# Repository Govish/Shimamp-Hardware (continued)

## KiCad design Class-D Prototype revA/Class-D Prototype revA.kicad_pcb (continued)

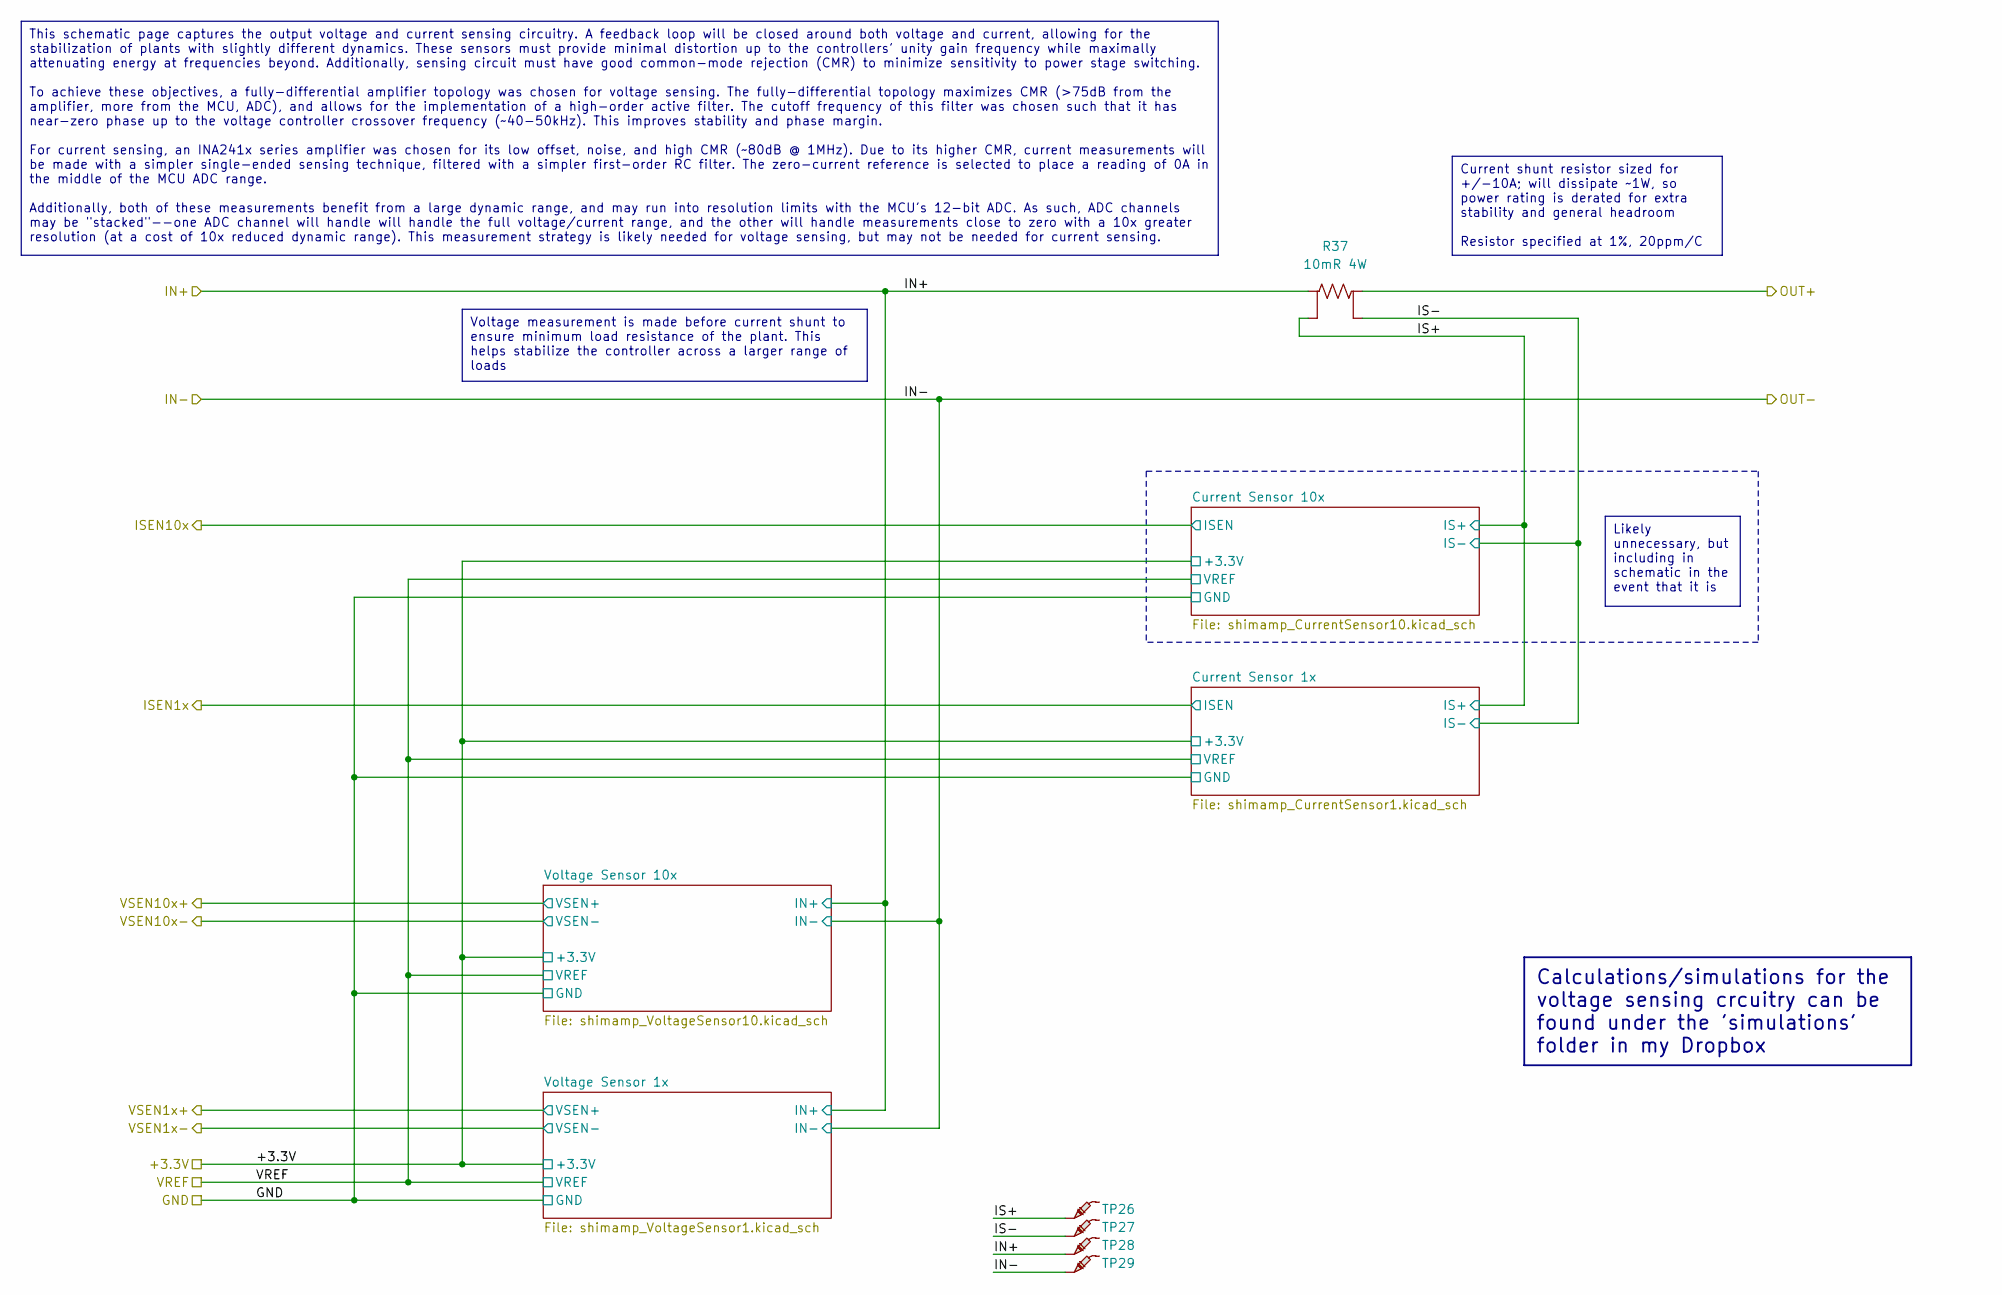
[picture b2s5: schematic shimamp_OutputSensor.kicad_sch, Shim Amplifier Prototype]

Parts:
R37: 10mR 4W; R_2512_6332_CURRENT_SHUNT; Part Number VMS-R010-1.0-U
TP26, TP27, TP28, TP29: -; TestPoint_Pad_D2.0mm

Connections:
/Output Sensor/IN+: R37.2, TP28.1; also elsewhere on the board
/Output Sensor/IN-: TP29.1; also elsewhere on the board
/Output Sensor/IS+: R37.4, TP26.1; also elsewhere on the board
/Output Sensor/IS-: R37.3, TP27.1; also elsewhere on the board
/Output Sensor/OUT+: R37.1; also elsewhere on the board

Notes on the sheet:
This schematic page captures the output voltage and current sensing circuitry. A feedback loop will be closed around both voltage and current, allowing for the stabilization of plants with slightly different dynamics. These sensors must provide minimal distortion up to the controllers' unity gain f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
Calculations/simulations for the voltage sensing crcuitry can be found under the 'simulations' folder in my Dropbox
Likely unnecessary, but including in schematic in the event that it is
Voltage measurement is made before current shunt to ensure minimum load resistance of the plant. This helps stabilize the controller across a larger range of loads
Current shunt resistor sized for +/-10A; will dissipate ~1W, so power rating is derated for extra stability and general headroom Resistor specified at 1%, 20ppm/C

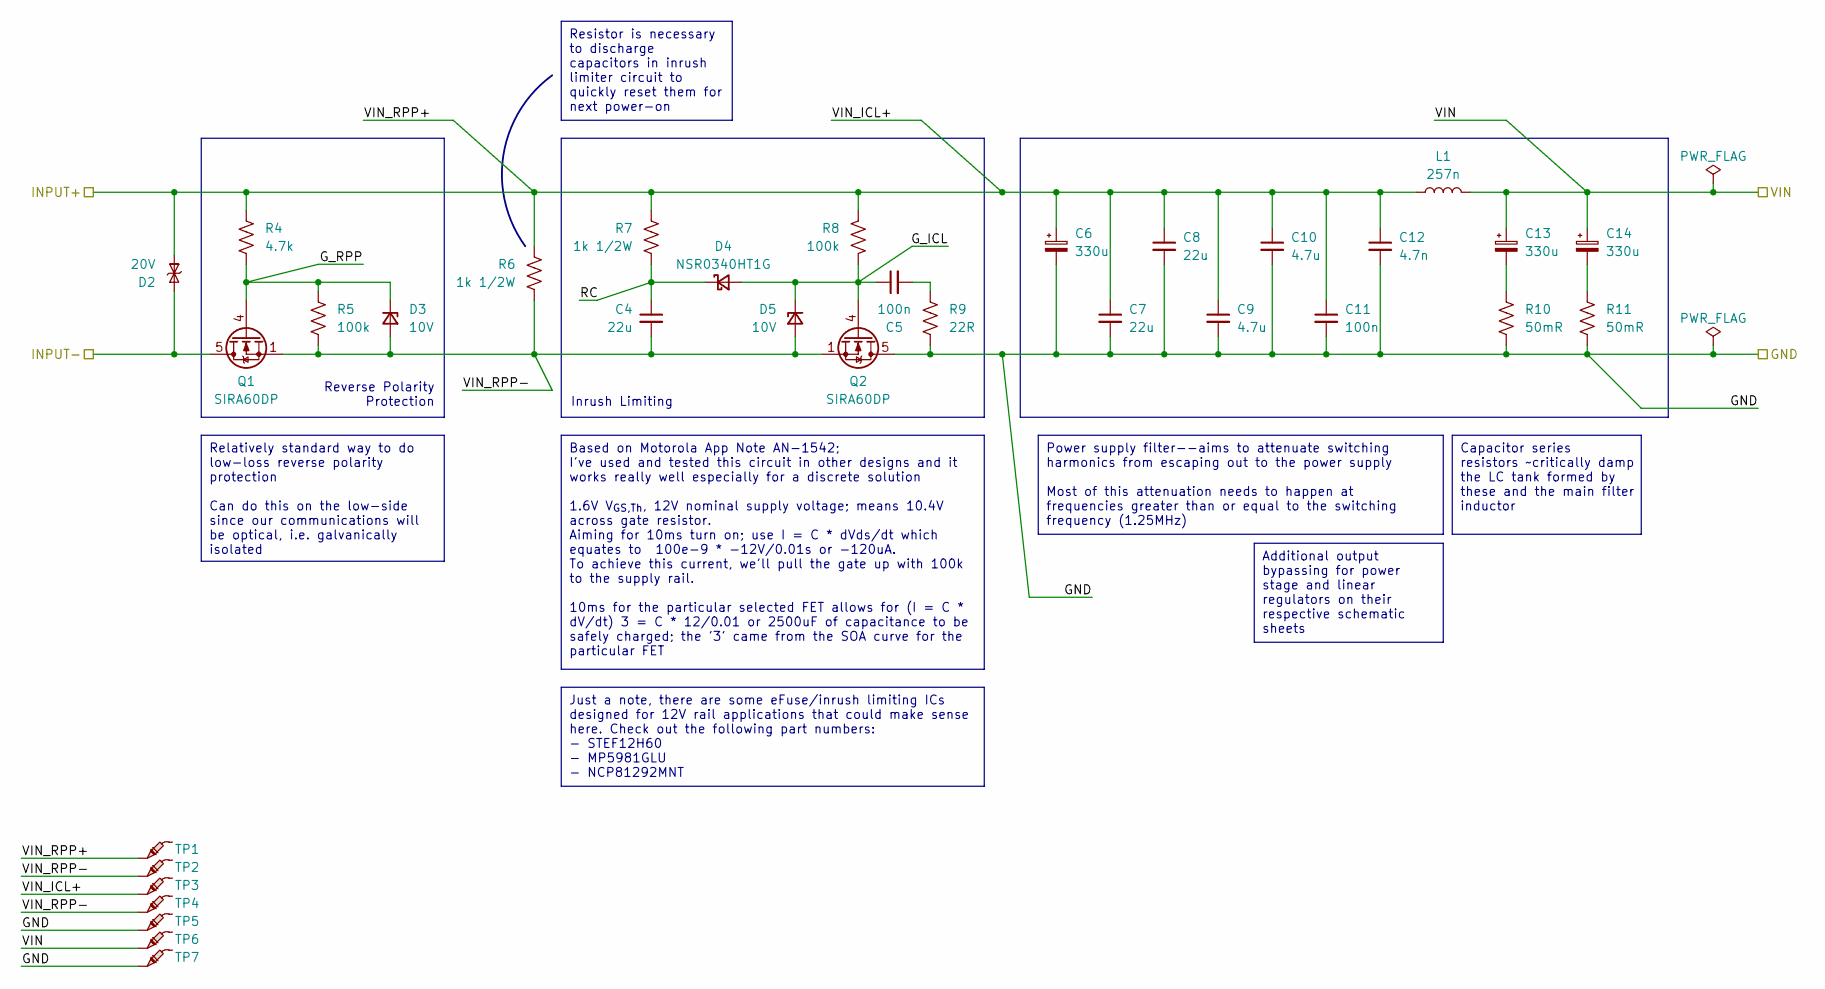
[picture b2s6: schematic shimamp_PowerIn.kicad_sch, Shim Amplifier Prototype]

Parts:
C4, C7, C8: 22u; C_1210_3225Metric_Pad1.33x2.70mm_HandSolder; Part Number CL32B226KAJNNNE
C5, C11: 100n; C_0603_1608Metric_Pad1.08x0.95mm_HandSolder; Part Number CL10B104KB8NNWC
C6, C13, C14: 330u; CP_Elec_10x12.6; Part Number 25SVPF330M
C9, C10: 4.7u; C_0805_2012Metric_Pad1.18x1.45mm_HandSolder; Part Number CL21A475KLCLQNC
C12: 4.7n; C_0402_1005Metric_Pad0.74x0.62mm_HandSolder; Part Number CL05B472KB5NNNC
D2: 20V; D_SMC; Part Number SMCJ20CA
D3, D5: 10V; D_SOD-323_HandSoldering; Part Number MM3Z10VC
D4: NSR0340HT1G; D_SOD-323_HandSoldering; Part Number NSR0340HT1G
L1: 257n; COILCRAFT_2014; Part Number 2014VS-251MED
Q1, Q2: SIRA60DP; PQFN-8-EP_6x5mm_P1.27mm_Generic; Part Number SIRA60DP-T1-GE3
R4: 4.7k; R_0603_1608Metric_Pad0.98x0.95mm_HandSolder; Part Number RMCF0603FT4K70
R5, R8: 100k; R_0603_1608Metric_Pad0.98x0.95mm_HandSolder; Part Number RMCF0603FT100K
R6, R7: 1k 1/2W; R_1210_3225Metric_Pad1.30x2.65mm_HandSolder; Part Number RMCF1210JT1K00
R9: 22R; R_0603_1608Metric_Pad0.98x0.95mm_HandSolder; Part Number RMCF0603FT22R0
R10, R11: 50mR; R_2512_6332Metric_Pad1.40x3.35mm_HandSolder; Part Number CSRN2512FK50L0
TP1, TP2, TP3, TP4, TP5, TP6, TP7: -; TestPoint_Pad_D2.0mm

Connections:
/Input Protection and Filtering/G_ICL: C5.1, D4.2 (A), D5.1 (K), Q2.4 (G), R8.2
/Input Protection and Filtering/G_RPP: D3.1 (K), Q1.4 (G), R4.2, R5.1
/Input Protection and Filtering/INPUT-: D2.2 (A), Q1.5 (D); also elsewhere on the board
/Input Protection and Filtering/RC: C4.1, D4.1 (K), R7.2
/Input Protection and Filtering/VIN_ICL+: C6.1, C7.1, C8.1, C9.1, C10.1, C11.1, C12.1, D2.1 (K), L1.1, R4.1, R6.1, R7.1, R8.1, TP1.1, TP3.1; also elsewhere on the board
/Input Protection and Filtering/VIN_RPP-: C4.2, D3.2 (A), D5.2 (A), Q1.1 (S), Q1.2 (S), Q1.3 (S), Q2.1 (S), Q2.2 (S), Q2.3 (S), R5.2, R6.2, TP2.1, TP4.1
GND: C6.2, C7.2, C8.2, C9.2, C10.2, C11.2, C12.2, Q2.5 (D), R9.2, R10.2, R11.2, TP5.1, TP7.1; also elsewhere on the board
unnamed: C5.2, R9.1
unnamed: C13.2, R10.1
unnamed: C14.2, R11.1
V_{IN}: C13.1, C14.1, L1.2, TP6.1; also elsewhere on the board

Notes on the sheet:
Additional output bypassing for power stage and linear regulators on their respective schematic sheets
Power supply filter--aims to attenuate switching harmonics from escaping out to the power supply Most of this attenuation needs to happen at frequencies greater than or equal to the switching frequency (1.25MHz)
Just a note, there are some eFuse/inrush limiting ICs designed for 12V rail applications that could make sense here. Check out the following part numbers: - STEF12H60 - MP5981GLU - NCP81292MNT
Based on Motorola App Note AN-1542; I've used and tested this circuit in other designs and it works really well especially for a discrete solution 1.6V V_{GS,Th}, 12V nominal supply voltage; means 10.4V across gate resistor. Aiming for 10ms turn on; use I = C * dVds/dt which equates to 100e-9 * -12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
Relatively standard way to do low-loss reverse polarity protection Can do this on the low-side since our communications will be optical, i.e. galvanically isolated
Resistor is necessary to discharge capacitors in inrush limiter circuit to quickly reset them for next power-on
Capacitor series resistors ~critically damp the LC tank formed by these and the main filter inductor
Inrush Limiting
Reverse Polarity Protection

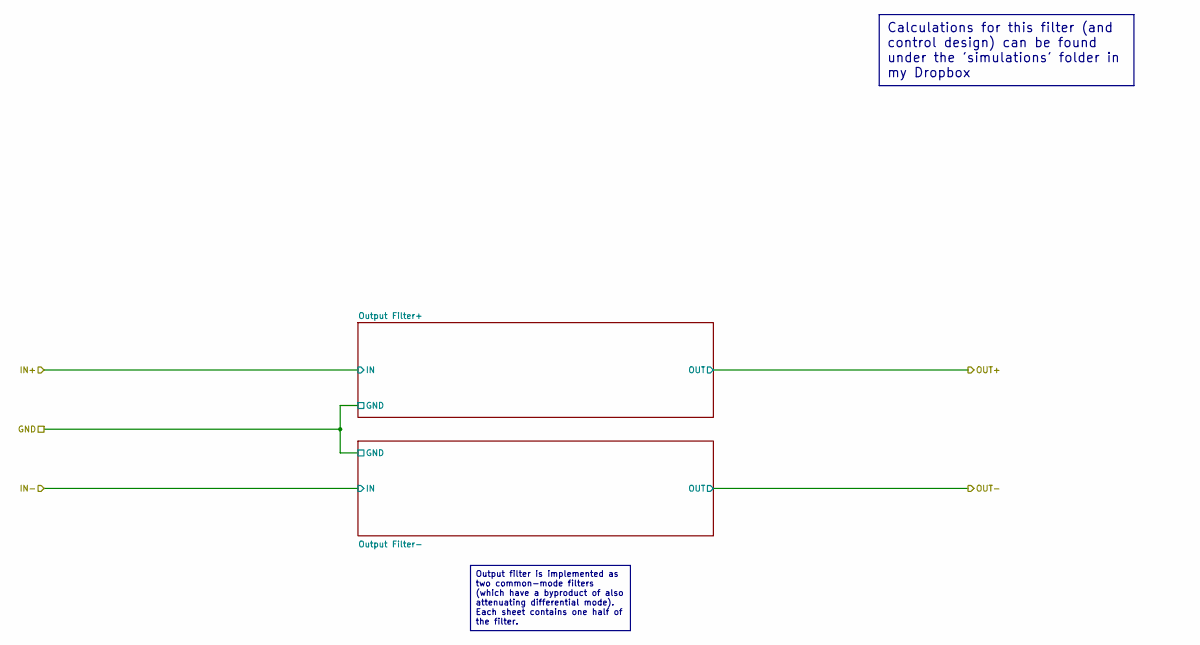
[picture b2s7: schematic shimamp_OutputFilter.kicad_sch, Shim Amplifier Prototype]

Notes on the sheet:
Output filter is implemented as two common-mode filters (which have a byproduct of also attenuating differential mode). Each sheet contains one half of the filter.
Calculations for this filter (and control design) can be found under the 'simulations' folder in my Dropbox

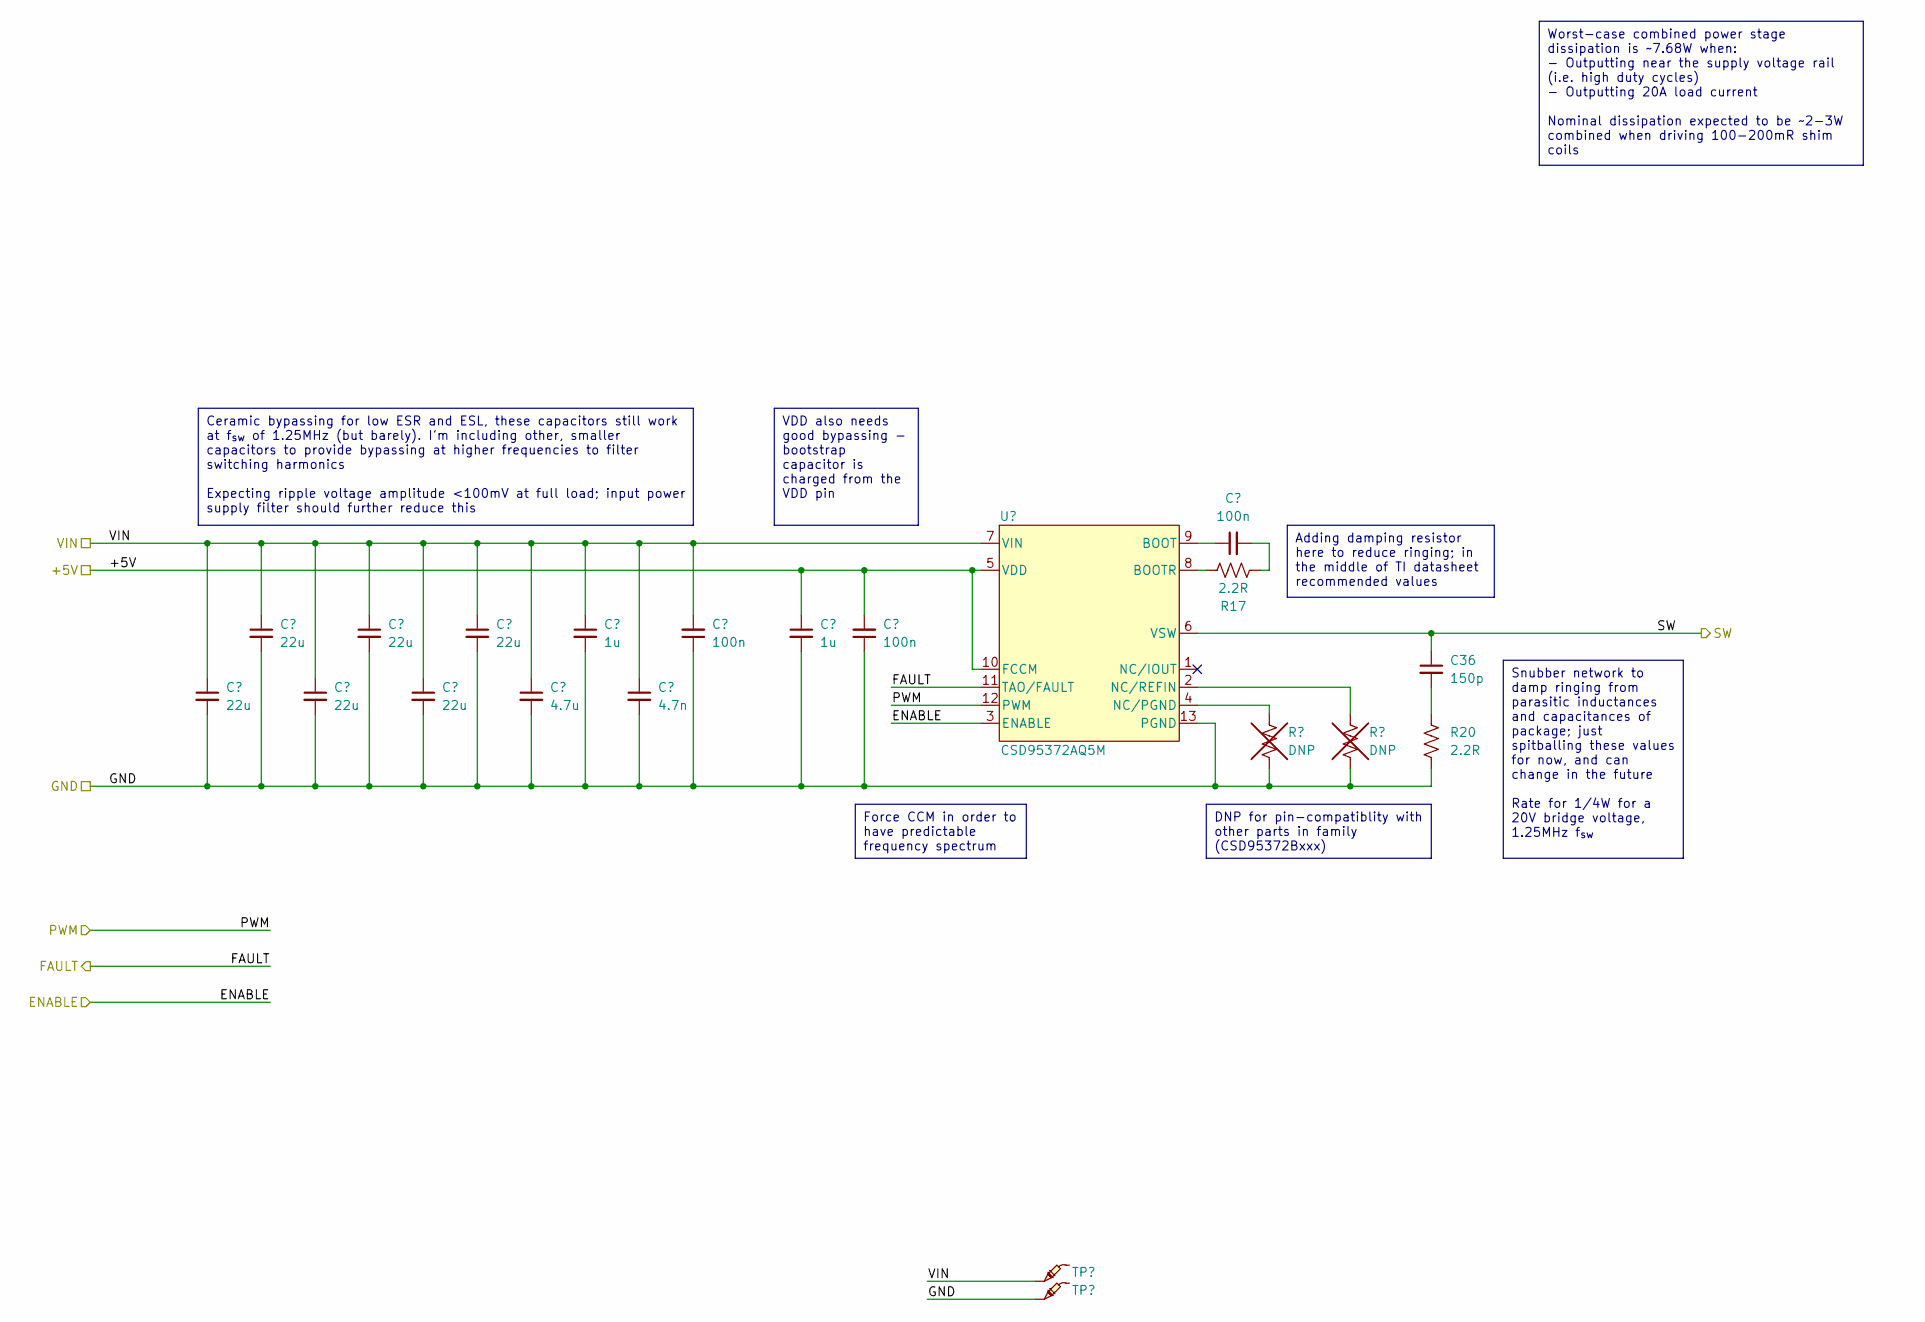
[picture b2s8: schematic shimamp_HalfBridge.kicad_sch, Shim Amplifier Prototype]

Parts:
C23, C24, C25, C26, C27, C28: 22u; C_1210_3225Metric_Pad1.33x2.70mm_HandSolder; Part Number CL32B226KAJNNNE
C29: 4.7u; C_0805_2012Metric_Pad1.18x1.45mm_HandSolder; Part Number CL21A475KLCLQNC
C30, C33: 1u; C_0805_2012Metric_Pad1.18x1.45mm_HandSolder; Part Number CL21B105KBFNNNG
C31: 4.7n; C_0402_1005Metric_Pad0.74x0.62mm_HandSolder; Part Number CL05B472KB5NNNC
C32, C34, C35: 100n; C_0603_1608Metric_Pad1.08x0.95mm_HandSolder; Part Number CL10B104KB8NNWC
C36: 150p; C_0603_1608Metric_Pad1.08x0.95mm_HandSolder; Part Number GCM1885C2A151JA16D
R17, R20: 2.2R; R_0805_2012Metric_Pad1.20x1.40mm_HandSolder; Part Number RPC0805JT2R20-UP
R18, R19: DNP; DNP_R_0603_1608Metric_Pad0.98x0.95mm_HandSolder
TP14, TP15: -; TestPoint_Pad_D2.0mm
U4: CSD95372AQ5M; LSON-12-1EP_5x6mm; Part Number CSD95372AQ5M

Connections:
+5V: C33.1, C34.2, U4.5 (VDD), U4.10 (FCCM); also elsewhere on the board
/ENABLE: U4.3 (ENABLE); also elsewhere on the board
/FAULT: U4.11 (TAO/FAULT); also elsewhere on the board
/Power Stage/Power Stage Half Bridge+/PWM: U4.12 (PWM); also elsewhere on the board
/Power Stage/Power Stage Half Bridge+/SW: C36.1, U4.6 (VSW); also elsewhere on the board
GND: C23.2, C24.2, C25.2, C26.2, C27.2, C28.2, C29.2, C30.2, C31.2, C32.1, C33.2, C34.1, R18.2, R19.2, R20.2, TP15.1, U4.13 (PGND); also elsewhere on the board
unnamed: C35.2, R17.2
unnamed: C36.2, R20.1
unnamed: C35.1, U4.9 (BOOT)
unnamed: R17.1, U4.8 (BOOTR)
unnamed: R18.1, U4.4 (NC/PGND)
unnamed: R19.1, U4.2 (NC/REFIN)
V_{IN}: C23.1, C24.1, C25.1, C26.1, C27.1, C28.1, C29.1, C30.1, C31.1, C32.2, TP14.1, U4.7 (VIN); also elsewhere on the board

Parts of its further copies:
C37, C38, C39, C40, C41, C42: 22u; C_1210_3225Metric_Pad1.33x2.70mm_HandSolder; Part Number CL32B226KAJNNNE
C43: 4.7u; C_0805_2012Metric_Pad1.18x1.45mm_HandSolder; Part Number CL21A475KLCLQNC
C44, C47: 1u; C_0805_2012Metric_Pad1.18x1.45mm_HandSolder; Part Number CL21B105KBFNNNG
C45: 4.7n; C_0402_1005Metric_Pad0.74x0.62mm_HandSolder; Part Number CL05B472KB5NNNC
C46, C48, C49: 100n; C_0603_1608Metric_Pad1.08x0.95mm_HandSolder; Part Number CL10B104KB8NNWC
C50: 150p; C_0603_1608Metric_Pad1.08x0.95mm_HandSolder; Part Number GCM1885C2A151JA16D
R21, R24: 2.2R; R_0805_2012Metric_Pad1.20x1.40mm_HandSolder; Part Number RPC0805JT2R20-UP
R22, R23: DNP; DNP_R_0603_1608Metric_Pad0.98x0.95mm_HandSolder
TP16, TP17: -; TestPoint_Pad_D2.0mm
U5: CSD95372AQ5M; LSON-12-1EP_5x6mm; Part Number CSD95372AQ5M

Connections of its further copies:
+5V: C47.1, C48.2, U5.5 (VDD), U5.10 (FCCM); also elsewhere on the board
/ENABLE: U5.3 (ENABLE); also elsewhere on the board
/FAULT: U5.11 (TAO/FAULT); also elsewhere on the board
/Power Stage/Power Stage Half Bridge-/PWM: U5.12 (PWM); also elsewhere on the board
/Power Stage/Power Stage Half Bridge-/SW: C50.1, U5.6 (VSW); also elsewhere on the board
GND: C37.2, C38.2, C39.2, C40.2, C41.2, C42.2, C43.2, C44.2, C45.2, C46.1, C47.2, C48.1, R22.2, R23.2, R24.2, TP17.1, U5.13 (PGND); also elsewhere on the board
unnamed: C49.2, R21.2
unnamed: C50.2, R24.1
unnamed: C49.1, U5.9 (BOOT)
unnamed: R21.1, U5.8 (BOOTR)
unnamed: R22.1, U5.4 (NC/PGND)
unnamed: R23.1, U5.2 (NC/REFIN)
V_{IN}: C37.1, C38.1, C39.1, C40.1, C41.1, C42.1, C43.1, C44.1, C45.1, C46.2, TP16.1, U5.7 (VIN); also elsewhere on the board

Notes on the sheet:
Worst-case combined power stage dissipation is ~7.68W when: - Outputting near the supply voltage rail (i.e. high duty cycles) - Outputting 20A load current Nominal dissipation expected to be ~2-3W combined when driving 100-200mR shim coils
Adding damping resistor here to reduce ringing; in the middle of TI datasheet recommended values
VDD also needs good bypassing - bootstrap capacitor is charged from the VDD pin
DNP for pin-compatiblity with other parts in family (CSD95372Bxxx)
Force CCM in order to have predictable frequency spectrum
Ceramic bypassing for low ESR and ESL, these capacitors still work at f_{sw} of 1.25MHz (but barely). I'm including other, smaller capacitors to provide bypassing at higher frequencies to filter switching harmonics Expecting ripple voltage amplitude <100mV at full load; input power supply filter sh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
Snubber network to damp ringing from parasitic inductances and capacitances of package; just spitballing these values for now, and can change in the future Rate for 1/4W for a 20V bridge voltage, 1.25MHz f_{sw}

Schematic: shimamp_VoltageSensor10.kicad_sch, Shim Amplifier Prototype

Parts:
C92: 100n; C_0603_1608Metric_Pad1.08x0.95mm_HandSolder; Part Number CL10B104KB8NNWC
C93, C94, C98, C99, C100: 1n; C_0603_1608Metric_Pad1.08x0.95mm_HandSolder; Part Number GCM1885C2A102FA16D
C95, C96: 470p; C_0603_1608Metric_Pad1.08x0.95mm_HandSolder; Part Number GCM1885C2A471FA16D
C97: 1u; C_0805_2012Metric_Pad1.18x1.45mm_HandSolder; Part Number CL21B105KBFNNNG
R38, R39: 2.2k 0.1%; R_1206_3216Metric_Pad1.30x1.75mm_HandSolder; Part Number RN73R2BTTD2201B25
R40, R41, R42, R43: 220R 0.1%; R_0603_1608Metric_Pad0.98x0.95mm_HandSolder; Part Number RN73R1JTTD2200B25
R44, R45: 75R 0.1%; R_0603_1608Metric_Pad0.98x0.95mm_HandSolder; Part Number RN73R1JTTD75R0B25
R46, R47: 4.7k; R_0603_1608Metric_Pad0.98x0.95mm_HandSolder; Part Number RMCF0603FT4K70
U6: LTC6362; MSOP-8_3x3mm_P0.65mm; Part Number LTC6362CMS8#TRPBF

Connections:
+3.3V: C92.1, C94.1, U6.3 (V+), U6.7 (~SHDN); also elsewhere on the board
/Output Sensor/IN+: R38.2; also elsewhere on the board
/Output Sensor/IN-: R39.2; also elsewhere on the board
/Output Sensor/Voltage Sensor 10x/V1+: C93.1, R38.1, R40.2, R42.2
/Output Sensor/Voltage Sensor 10x/V1-: C93.2, R39.1, R41.2, R43.2
/Output Sensor/Voltage Sensor 10x/V2+: C95.1, R40.1, U6.8 (+)
/Output Sensor/Voltage Sensor 10x/V2-: C96.1, R41.1, U6.1 (-)
/Output Sensor/Voltage Sensor 10x/VO+: C95.2, R42.1, R44.2, U6.5
/Output Sensor/Voltage Sensor 10x/VO-: C96.2, R43.1, R45.2, U6.4
/Output Sensor/Voltage Sensor 10x/V_{OCM}: C97.1, R46.2, R47.1, U6.2 (V_{OCM})
/VSEN10x+: C98.2, C99.1, R45.1; also elsewhere on the board
/VSEN10x-: C98.1, C100.1, R44.1; also elsewhere on the board
GND: C92.2, C94.2, C97.2, C99.2, C100.2, R47.2, U6.6 (V-); also elsewhere on the board
V_{REF}: R46.1; also elsewhere on the board

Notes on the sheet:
LTC6362 chosen for good offset/noise performance; THS453x may also be a good part candidate (similar pinout but slightly different package)
3rd-order butterworth mutiple feedback filter with ~750kHz cutoff frequency (slight mismatch to the 10x amplifier), *10x* attenuation Want high-accuracy resistors and capacitors to ensure good matching between positive and negative branches; this ensures good CMR
All caps here are NP0/C0G tolerance
Rate these resistors for 1/4W to accomodate non-zero input impedance
Can measure power stage voltages of +/-20V (i.e. half of bridge is tied to GND, other half is driving load)
High absolute accuracy of common-mode reference is not super necessary since voltage will be sensed differentially; Only really care about low noise at this node RC formed by divider resistors and cap should roll off around 67Hz

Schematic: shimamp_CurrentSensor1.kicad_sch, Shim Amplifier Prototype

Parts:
C113, C115: 1n; C_0603_1608Metric_Pad1.08x0.95mm_HandSolder; Part Number GCM1885C2A102FA16D
C114: 100n; C_0603_1608Metric_Pad1.08x0.95mm_HandSolder; Part Number CL10B104KB8NNWC
R59: 750R; R_0603_1608Metric_Pad0.98x0.95mm_HandSolder; Part Number RMCF0603FT750R
U9: INA241A1; SOT-23-8_Handsoldering; Part Number INA241A1IDDFR

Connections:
+3.3V: C114.1, U9.6 (VS); also elsewhere on the board
/ISEN1x: C115.1, R59.1; also elsewhere on the board
/Output Sensor/IS+: U9.8 (+); also elsewhere on the board
/Output Sensor/IS-: U9.1 (-); also elsewhere on the board
GND: C113.2, C114.2, C115.2, U9.2 (GND), U9.4 (GND), U9.7 (REF1); also elsewhere on the board
unnamed: R59.2, U9.5
V_{REF}: C113.1, U9.3 (REF2); also elsewhere on the board

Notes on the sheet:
Current sense is a single-ended measurement; filter rolls off ~212kHz
ADC range is from 0 to 2.048V--center the zero-current reading at 1.024V +/-10A thru 10mR with 10x gain should provide an output range of 0.024V to 2.024V
Reference divider is like insanely (ratiometrically) accurate, +/-0.005% maximum for the grade of part specified in this schematic; We'll never be able to easily generate something that accurate, so let's just leverage the chip's divider accuracy to generate the "zero-current reference voltage". Th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
Voltage reference can take a total of 10nF load capacitance at its output

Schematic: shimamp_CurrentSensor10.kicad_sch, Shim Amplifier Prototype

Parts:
C110, C112: 1n; C_0603_1608Metric_Pad1.08x0.95mm_HandSolder; Part Number GCM1885C2A102FA16D
C111: 100n; C_0603_1608Metric_Pad1.08x0.95mm_HandSolder; Part Number CL10B104KB8NNWC
R58: 750R; R_0603_1608Metric_Pad0.98x0.95mm_HandSolder; Part Number RMCF0603FT750R
U8: INA241A4; SOT-23-8_Handsoldering; Part Number INA241A4IDDFR

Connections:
+3.3V: C111.1, U8.6 (VS); also elsewhere on the board
/ISEN10x: C112.1, R58.1; also elsewhere on the board
/Output Sensor/IS+: U8.8 (+); also elsewhere on the board
/Output Sensor/IS-: U8.1 (-); also elsewhere on the board
GND: C110.2, C111.2, C112.2, U8.2 (GND), U8.4 (GND), U8.7 (REF1); also elsewhere on the board
unnamed: R58.2, U8.5
V_{REF}: C110.1, U8.3 (REF2); also elsewhere on the board

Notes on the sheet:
Voltage reference can take a total of 10nF load capacitance at its output
Reference divider is like insanely (ratiometrically) accurate, +/-0.005% maximum for the grade of part specified in this schematic; We'll never be able to easily generate something that accurate, so let's just leverage the chip's divider accuracy to generate the "zero-current reference voltage". Th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
Current sense is a single-ended measurement; filter rolls off ~212kHz
ADC range is from 0 to 2.048V--center the zero-current reading at 1.024V +/-1A thru 10mR with 100x gain should provide an output range of 0.024V to 2.024V

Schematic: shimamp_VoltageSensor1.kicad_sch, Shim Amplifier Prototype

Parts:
C101: 100n; C_0603_1608Metric_Pad1.08x0.95mm_HandSolder; Part Number CL10B104KB8NNWC
C102: 150p; C_0603_1608Metric_Pad1.08x0.95mm_HandSolder; Part Number GCM1885C2A151JA16D
C103, C107, C108, C109: 1n; C_0603_1608Metric_Pad1.08x0.95mm_HandSolder; Part Number GCM1885C2A102FA16D
C104, C105: 33p; C_0603_1608Metric_Pad1.08x0.95mm_HandSolder; Part Number GCM1885C2A330JA16D
C106: 1u; C_0805_2012Metric_Pad1.18x1.45mm_HandSolder; Part Number CL21B105KBFNNNG
R48, R49, R50, R51, R52, R53: 2.2k 0.1%; R_1206_3216Metric_Pad1.30x1.75mm_HandSolder; Part Number RN73R2BTTD2201B25
R54, R55: 75R 0.1%; R_0603_1608Metric_Pad0.98x0.95mm_HandSolder; Part Number RN73R1JTTD75R0B25
R56, R57: 4.7k; R_0603_1608Metric_Pad0.98x0.95mm_HandSolder; Part Number RMCF0603FT4K70
U7: LTC6362; MSOP-8_3x3mm_P0.65mm; Part Number LTC6362CMS8#TRPBF

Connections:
+3.3V: C101.1, C103.1, U7.3 (V+), U7.7 (~SHDN); also elsewhere on the board
/Output Sensor/IN+: R48.2; also elsewhere on the board
/Output Sensor/IN-: R49.2; also elsewhere on the board
/Output Sensor/Voltage Sensor 1x/V1+: C102.1, R48.1, R50.2, R52.2
/Output Sensor/Voltage Sensor 1x/V1-: C102.2, R49.1, R51.2, R53.2
/Output Sensor/Voltage Sensor 1x/V2+: C104.1, R50.1, U7.8 (+)
/Output Sensor/Voltage Sensor 1x/V2-: C105.1, R51.1, U7.1 (-)
/Output Sensor/Voltage Sensor 1x/VO+: C104.2, R52.1, R54.2, U7.5
/Output Sensor/Voltage Sensor 1x/VO-: C105.2, R53.1, R55.2, U7.4
/Output Sensor/Voltage Sensor 1x/V_{OCM}: C106.1, R56.2, R57.1, U7.2 (V_{OCM})
/VSEN1x+: C107.2, C108.1, R55.1; also elsewhere on the board
/VSEN1x-: C107.1, C109.1, R54.1; also elsewhere on the board
GND: C101.2, C103.2, C106.2, C108.2, C109.2, R57.2, U7.6 (V-); also elsewhere on the board
V_{REF}: R56.1; also elsewhere on the board

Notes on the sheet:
All caps here are NP0/C0G tolerance
LTC6362 chosen for good offset/noise performance; THS453x may also be a good part candidate (similar pinout but slightly different package)
Rate these resistors for 1/4W to accomodate non-zero input impedance
Can measure power stage voltages of +/-2V (i.e. half of bridge is tied to GND, other half is driving load) Amplifier inputs can be over-driven to +/-20V safely, though output will saturate
3rd-order butterworth mutiple feedback filter with ~730kHz cutoff frequency (slight mismatch to the 10x amplifier), *1x* attenuation Want high-accuracy resistors and capacitors to ensure good matching between positive and negative branches; this ensures good CMR
High absolute accuracy of common-mode reference is not super necessary since voltage will be sensed differentially; Only really care about low noise at this node RC formed by divider resistors and cap should roll off around 67Hz

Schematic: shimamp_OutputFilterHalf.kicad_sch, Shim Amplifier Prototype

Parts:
C51, C52: 220u; CP_Elec_10x12.5; Part Number 875075561008
C53, C54, C55, C56, C57: 22u; C_1210_3225Metric_Pad1.33x2.70mm_HandSolder; Part Number CL32B226KAJNNNE
C58: 4.7u; C_0805_2012Metric_Pad1.18x1.45mm_HandSolder; Part Number CL21A475KLCLQNC
C59, C60, C65, C66: 100n; C_0603_1608Metric_Pad1.08x0.95mm_HandSolder; Part Number CL10B104KB8NNWC
C61, C62, C67, C68: 4.7n; C_0402_1005Metric_Pad0.74x0.62mm_HandSolder; Part Number CL05B472KB5NNNC
C63, C64: 1u; C_0805_2012Metric_Pad1.18x1.45mm_HandSolder; Part Number CL21B105KBFNNNG
L2, L3: 257n; COILCRAFT_2014; Part Number 2014VS-251MED
L4: 90n; COILCRAFT_1212; Part Number 1212VS-90NMED
L5: 22n; WURTH_3168; Part Number 744914122
R25: 120m; R_1206_3216Metric_Pad1.30x1.75mm_HandSolder; Part Number MFHA1206R1200FC
TP18, TP19, TP20, TP21: -; TestPoint_Pad_D2.0mm

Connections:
/Output Filter/Output Filter+/FILT_MID: C51.1, C52.1, C53.1, C54.1, C55.1, C56.1, C57.1, C58.1, C59.1, C60.1, C61.1, C62.1, L3.1, L4.1, R25.1, TP18.1
/Output Sensor/IN+: C63.1, C64.1, C65.1, C66.1, C67.1, C68.1, L4.2, L5.2, TP20.1; also elsewhere on the board
/Power Stage/Power Stage Half Bridge+/SW: L2.2; also elsewhere on the board
GND: C51.2, C52.2, C53.2, C54.2, C55.2, C56.2, C57.2, C58.2, C59.2, C60.2, C61.2, C62.2, C63.2, C64.2, C65.2, C66.2, C67.2, C68.2, TP19.1, TP21.1; also elsewhere on the board
unnamed: L2.1, L3.2
unnamed: L5.1, R25.2

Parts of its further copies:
C69, C70: 220u; CP_Elec_10x12.5; Part Number 875075561008
C71, C72, C73, C74, C75: 22u; C_1210_3225Metric_Pad1.33x2.70mm_HandSolder; Part Number CL32B226KAJNNNE
C76: 4.7u; C_0805_2012Metric_Pad1.18x1.45mm_HandSolder; Part Number CL21A475KLCLQNC
C77, C78, C83, C84: 100n; C_0603_1608Metric_Pad1.08x0.95mm_HandSolder; Part Number CL10B104KB8NNWC
C79, C80, C85, C86: 4.7n; C_0402_1005Metric_Pad0.74x0.62mm_HandSolder; Part Number CL05B472KB5NNNC
C81, C82: 1u; C_0805_2012Metric_Pad1.18x1.45mm_HandSolder; Part Number CL21B105KBFNNNG
L6, L7: 257n; COILCRAFT_2014; Part Number 2014VS-251MED
L8: 90n; COILCRAFT_1212; Part Number 1212VS-90NMED
L9: 22n; WURTH_3168; Part Number 744914122
R26: 120m; R_1206_3216Metric_Pad1.30x1.75mm_HandSolder; Part Number MFHA1206R1200FC
TP22, TP23, TP24, TP25: -; TestPoint_Pad_D2.0mm

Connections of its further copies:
/Output Filter/Output Filter-/FILT_MID: C69.1, C70.1, C71.1, C72.1, C73.1, C74.1, C75.1, C76.1, C77.1, C78.1, C79.1, C80.1, L7.1, L8.1, R26.1, TP22.1
/Output Sensor/IN-: C81.1, C82.1, C83.1, C84.1, C85.1, C86.1, L8.2, L9.2, TP24.1; also elsewhere on the board
/Power Stage/Power Stage Half Bridge-/SW: L6.2; also elsewhere on the board
GND: C69.2, C70.2, C71.2, C72.2, C73.2, C74.2, C75.2, C76.2, C77.2, C78.2, C79.2, C80.2, C81.2, C82.2, C83.2, C84.2, C85.2, C86.2, TP23.1, TP25.1; also elsewhere on the board
unnamed: L6.1, L7.2
unnamed: L9.1, R26.2

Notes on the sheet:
This is one half of a 2-stage, 4th-order filter that provides both differential and common-mode filtering. Since the control loop bandwidth is greater than the resonant frequency of the first filter stage, it can remain undamped. However, this is not the case with the second stage, requiring the in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
Calculations for this filter (and control design) can be found under the 'simulations' folder in my Dropbox
- Aluminum Poly caps are good up to about ~2-300kHz - 22u ceramics are good to ~1MHz - 4.7u, 1u ceramics are good to ~8MHz - 100n ceramics are good to ~20MHz - 4.7n ceramics resonate at ~150MHz Ceramics will derate about 75% (i.e. 25% of their value) at 12V DC Bias Except for the 1u caps those only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
Paralleled aluminum polymer capacitors for lower ESR and higher ripple rating; good for 100's of kHz; Inductor Ripple current ~4.75A worst case (50% duty cycle) with 12V supply, 1.25MHz switching; should result in <40mV ripple at the end of the first stage
In the board design, give the smallest capacitors the tightest loops; this will minimize parasitic inductance for those components where it matters most.
